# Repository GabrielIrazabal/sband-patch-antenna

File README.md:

# S-band patch antenna (SSI 1U CubeSat), rev 1

Right-hand circularly polarized patch antenna for the satellite's S-band TT&C link (uplink and downlink, around 2.4 GHz). This repo holds the rev-1 KiCad boards, order-ready Gerbers, the simulations behind them and the design notes.

Research doc: PJ-10004, S-band patch antenna research (internal to SSI) · Author: Gabriel Irazabal

> **Using an AI assistant?** Point it at this repo. It should read [`CLAUDE.md`](CLAUDE.md) first.
>
> **Running the Ansys HFSS check on the Windows laptop?** Everything is in [`HFSS_TASK.md`](HFSS_TASK.md).

## Status

| Step | State |
| --- | --- |
| Requirements and design decisions | Done |
| Simulation (openEMS) | Done for five boards: two designs × two materials, plus a cut-corner PTFE board tuned for the satellite face |
| KiCad boards, size variants, Gerbers | Done for all four antenna options below, zips in [`fab/`](fab). The 3 mm boards still have open questions for JLC |
| **Decision needed: board material** | RO4350B does not reach the 6.5 dBic gain requirement; JLC's PTFE does once mounted on the satellite. See [Gain](#gain-the-one-requirement-not-met-on-ro4350b) |
| Cross-check in HFSS | Done. HFSS agrees within 0.4 % in frequency and 0.3 dB in gain. See [`sim/HFSS_RESULTS.md`](sim/HFSS_RESULTS.md) |
| Rerun check, 24 November | All four re-simulated in openEMS: three pass in both solvers, the 1.5 mm dual feed is borderline. See [`sim/RERUN_CHECK.md`](sim/RERUN_CHECK.md). HFSS rerun on the laptop: [`HFSS_RERUN.md`](HFSS_RERUN.md) |
| JLC order, VNA test | Not done |

## The four antenna options and their files

All four are on JLC's PTFE (ZYF255DA), 60 × 60 mm, tuned in HFSS for 2.425 GHz on a 100 mm metal face. Numbers are HFSS, across the 20 MHz channel; nothing has been built. Plots: [`docs/results_60mm/`](docs/results_60mm/README.md).

| Antenna | Patch / feed / cut (mm) | RHCP gain | Worst axial ratio | KiCad | Gerbers |
| --- | --- | --- | --- | --- | --- |
| Cut corner, 1.5 mm | 37.52 / 7.00 / 3.50 | 7.08–7.24 dBic | 4.14 dB | [`kicad/Cutcorner_antenna`](kicad/Cutcorner_antenna) (drawn by hand) | `fab/Cutcorner_antenna.zip` |
| Dual feed, 1.5 mm | 37.28 / 5.80 / none | 6.75–6.96 dBic | 0.79 dB | [`kicad/A_dualfeed_PTFE_face100`](kicad/A_dualfeed_PTFE_face100) | `fab/A_dualfeed_PTFE_face100.zip`, plus `_L36p98` and `_L37p58` |
| Cut corner, 3 mm | 37.10 / 8.00 and 2.18 sideways / 5.55 | 7.61–7.67 dBic | 2.17 dB | [`kicad/prototype_thick`](kicad/prototype_thick): `B_cutcorner_RHCP_PTFE_3mm_TOP` and `_BOTTOM` | `fab/B_cutcorner_RHCP_PTFE_3mm_TOP.zip` and `_BOTTOM.zip` |
| Dual feed, 3 mm | 36.39 / 6.70 / none | 7.26–7.32 dBic | 0.94 dB | [`kicad/prototype_thick`](kicad/prototype_thick): `A_dualfeed_PTFE_3mm_TOP` and `_BOTTOM` | `fab/A_dualfeed_PTFE_3mm_TOP.zip` and `_BOTTOM.zip` |

- Dual-feed figures assume a typical 90° coupler (0.5 dB and 3° off, 0.4 dB loss). The coupler is an external part.
- **The 1.5 mm cut corner here is the hand-drawn board.** It has the same dimensions as the generated `B_cutcorner_RHCP_PTFE_face100`, with the whole top side free of solder mask. The generated board and its ±0.3 mm variants are still in `kicad/` and `fab/`.
- **The 3 mm antennas are each two boards** glued face to face: a TOP board with only the patch and a BOTTOM board with only the ground and connector. Read the open points in [`kicad/prototype_thick/README.md`](kicad/prototype_thick/README.md) before ordering them.
- **These sizes are for PTFE only.** On RO4350B the same patch would resonate near 2.04 GHz. The RO4350B boards are the ones in the table under [The boards](#the-boards).
- Every board except the generated rev-1 ones has its whole top side free of solder mask, because HFSS showed mask around the patch shifts the tuning by 6 to 8 MHz.

## Requirements and how the designs compare

Simulated on the bare 60 × 60 mm board at 2.425 GHz. Board A assumes an ideal 90° hybrid.

| Requirement | Target | A, RO4350B | B, RO4350B | A, PTFE | B, PTFE |
| --- | --- | --- | --- | --- | --- |
| Frequency | 2.4 GHz band (design centre 2.425 GHz) | ✓ | ✓ | ✓ | ✓ |
| Match across 20 MHz | return loss ≥ 10 dB | ✓ 13.5 dB | ✓ 12.2 dB | ✓ 14.3 dB | ✓ 11.6 dB |
| Gain | ≥ 6.5 dBic, ideally 7+ | ✗ 5.6–5.8 | ✗ 5.5–5.7 | ✗ 6.3–6.4 | ✗ 6.1–6.3 |
| Gain on a 100 mm metal face | same | ✗ 5.9–6.0 | ✗ 6.0–6.1 | ✓ 6.8–6.9 | ✓ 6.7–6.9 |
| Half-power beamwidth | ≥ 60° | ✓ 88° | ✓ 88° | ✓ 84° | ✓ 84° |
| Polarization | RHCP | ✓ | ✓ | ✓ | ✓ |
| Axial ratio across 20 MHz | ≤ 3 dB | set by the hybrid | ✗ 3.5 dB at the edges | set by the hybrid | ✗ 3.4 dB at the edges |
| Impedance | 50 Ω | ✓ | ✓ | ✓ | ✓ |
| Power handling | ≥ 3 W | SMA: yes. Not otherwise analysed | | | |
| Environment | −40 to +85 °C | Not simulated directly; see drift below | | | |
| Connector | SMA | ✓ surface-mount vertical SMA | | | |

Notes on reading this table:
- **Board A's gain is before the hybrid's own loss**, typically 0.3–0.5 dB. Board B has no hybrid.
- **Board A's axial ratio** depends on the hybrid's amplitude and phase balance, not on the patch. With both ports simulated separately the patch itself gives 0.2–0.3 dB.
- **A 3.4–3.5 dB axial ratio at the band edge** costs about 0.15 dB against a perfectly circular ground antenna.
- **The 60° beamwidth target** is met with margin: at 30° off boresight the gain is down about 1.5 dB (2.0–2.2 dB on the 100 mm face).

## Gain: the one requirement not met on RO4350B

The patch's directivity is fixed mostly by its size and ground plane. What's left after losses in the board and copper is the gain.

Best achievable gain (directivity × radiation efficiency, perfect match, no hybrid loss):

| Material, thickness | Directivity | Efficiency | Bare 60 mm board | On a 100 mm metal face |
| --- | --- | --- | --- | --- |
| RO4350B, 1.52 mm | 6.7 dBi | 82–84 % | 5.9 dBic | 6.3 dBic |
| RO4350B, 3.05 mm (two boards stacked) | 6.7 dBi | 91 % | 6.3 dBic | 6.8 dBic |
| PTFE ZYF255DA, 1.52 mm | 7.1 dBi | 89 % | 6.6 dBic | 7.2 dBic |
| PTFE ZYF255DA, 3.05 mm (stacked) | 7.1 dBi | 94 % | 6.8 dBic | 7.5 dBic |

- **RO4350B at 1.52 mm cannot reach 6.5 dBic** in any simulated configuration.
- **PTFE at 1.52 mm reaches it once mounted on the satellite**: the larger patch (about 37 mm) has more directivity, and the material loses less.
- **A cut-corner PTFE board tuned for the 100 mm face reaches 6.8–7.05 dBic** across the band (`B_cutcorner_RHCP_PTFE_face100`). That is the only simulated 1.52 mm board that touches "ideally 7+"; getting comfortably past 7 needs PTFE and more thickness.
- The 100 mm face is modeled as a flat metal plate behind the board. A real 1U body with solar panels will differ somewhat.
- Mission Control's link budget assumed a 5 dBi linear patch with a 3 dB polarization loss. Every board here beats that assumption.

Trade-offs of moving to PTFE (ZYF255DA):

| | RO4350B | ZYF255DA (PTFE) |
| --- | --- | --- |
| Dk / loss tangent | 3.66 (design) / 0.0031 | 2.55 / 0.0018 (JLC listing) |
| Patch side at 2.425 GHz | 31.4 mm | 37.4 mm (fits the 60 mm board) |
| Gain | about 0.7 dB lower | about 0.7 dB higher |
| JLC price | about $185 for 5 | lower when quoted in October |
| Space heritage, outgassing data | widely flown; TML 0.12 %, CVCM 0.02 % | **no outgassing data found for this laminate** |
| Dk used for design | Rogers publishes a design value | JLC's listed value, not independently verified |

## The boards

| | Top | Bottom |
| --- | --- | --- |
| **A: dual feed** (RO4350B) |  |  |
| **B: cut corner** (RO4350B) |  |  |
| **A-PTFE** |  |  |
| **B-PTFE** |  |  |

Simulated dimensions (mm):

| Board | Patch side | Feed offset from centre | Corner cut leg | Size variants built |
| --- | --- | --- | --- | --- |
| `A_dualfeed` | 31.40 | 5.80 | none | 31.10, 31.70 |
| `B_cutcorner_RHCP` | 31.54 | 5.90 | 3.13 | 31.24, 31.84 |
| `A_dualfeed_PTFE` | 37.38 | 6.90 | none | 37.08, 37.68 |
| `B_cutcorner_RHCP_PTFE` | 37.56 | 7.00 | 3.80 | 37.26, 37.86 |
| `B_cutcorner_RHCP_PTFE_face100` | 37.52 | 7.00 | 3.50 | 37.22, 37.82 |

`B_cutcorner_RHCP_PTFE_face100` looks the same as B-PTFE but is tuned for mounting flat on a 100 mm metal face. On that face it simulates at 0.2 dB best axial ratio at 2.425 GHz, 3.9 dB at the band edges, and 6.8–7.05 dBic. Use it only if the antenna really mounts that way.

Common to all:
- 60 × 60 mm, 2 layers, 1.52 mm core, ENIG.
- **Top:** only the patch, with no solder mask over it.
- **Bottom:** solid ground, M3 mounting holes 4 mm from each corner (placeholder positions).
- **Feed:** surface-mount vertical SMA (Würth WR-SMA 60312102114405) on the bottom, soldered flat to the ground so no legs pass through the patch. A 0.5 mm plated via under its centre pad is the probe up to the patch.
- **Board A:** J1 on the +x axis, J2 on the +y axis (up in the top view). **RHCP when J2 lags J1 by 90°**; this is printed on the back. It has no hybrid on the board: test it with an external connectorized 90° hybrid and two equal-length cables.
- **Board B:** top-left and bottom-right corners cut (top view). **Confirmed RHCP** two ways: from the simulated far field, and from the rotation of the raw field over time above the patch.
- The size variants cover frequency error: 0.3 mm of patch side is about 21 MHz on RO4350B and 19 MHz on PTFE.

## Simulation results

Solver: openEMS (FDTD). Details and the full run list are in [`sim/README.md`](sim/README.md); raw outputs are in [`sim/results_openems/`](sim/results_openems).

| Board | Plot |
| --- | --- |
| A, RO4350B |  |
| B, RO4350B |  |
| A, PTFE |  |
| B, PTFE |  |

Detail (bare 60 mm board unless stated):

| | A, RO4350B | B, RO4350B | A, PTFE | B, PTFE |
| --- | --- | --- | --- | --- |
| Worst S11 in the 20 MHz band | −13.5 dB | −12.2 dB | −14.3 dB | −11.6 dB |
| −10 dB match bandwidth | 35.5 MHz | 69 MHz | 37.5 MHz | 71 MHz |
| Isolation between ports | −39 dB | n/a | −39 dB | n/a |
| Best axial ratio | hybrid-set | 0.2 dB | hybrid-set | 0.3 dB |
| Axial ratio ≤ 3 dB bandwidth | hybrid-set | about 15–18 MHz | hybrid-set | about 15–18 MHz |
| RHCP gain in band | 5.6–5.8 dBic | 5.5–5.7 dBic | 6.3–6.4 dBic | 6.1–6.3 dBic |
| RHCP gain on the 100 mm face | 5.9–6.0 dBic | 6.0–6.1 dBic | 6.8–6.9 dBic | 6.7–6.9 dBic |
| Half-power beamwidth (on the 100 mm face) | 88° (74–76°) | 88° (74–76°) | 84° (72–74°) | 84° (72–74°) |

### Sensitivity to board material (Dk off by ±1 %)

| | A, RO4350B | B, RO4350B | A, PTFE | B, PTFE |
| --- | --- | --- | --- | --- |
| Frequency shift | ±12.5 MHz | ±12.5 MHz | ±11.5 MHz | ±11.5 MHz |
| Worst S11 in band | −8.5 dB | −10 dB | −9.2 dB | −10.2 dB |
| Worst axial ratio in band | unaffected | 7.5 dB | unaffected | 6.8 dB |
| Lowest RHCP gain in band | 5.2 dBic | 4.8 dBic | 5.95 dBic | 5.6 dBic |

Board A tolerates material and temperature drift better: its polarization is set by the hybrid, so a frequency shift only costs some match. Board B's polarization degrades directly.

### Effect of the ground it's mounted on

A larger ground raises gain by about 0.5 dB and narrows the resonance (RO4350B match bandwidth 36 → 26 MHz). On the 100 mm face, board B's best axial ratio degrades from 0.2–0.3 dB to 1.3–1.5 dB because its corner cut was tuned for the bare board. **Board B needs re-tuning for the real mounting; board A does not.**

Re-tuning works as predicted: shrinking the PTFE board's cut from 3.80 to 3.50 mm (and the patch from 37.56 to 37.52 mm) brought the axial ratio on the 100 mm face back to 0.2 dB at 2.425 GHz.

### What the simulation does and doesn't establish

- **Frequency accuracy is about ±1 %.** Two published measured patches on εr 2.5, 1.524 mm board simulate 0.4–0.9 % low: 41.4 × 41.0 mm (measured 2.228 GHz, simulated 2.208–2.217) and 41.4 × 68.58 mm (measured 2.200 GHz, simulated 2.185–2.192). The measured values were recalled from the literature, not re-read, so treat this as supporting evidence.
- **Real boards may therefore land 10–20 MHz high.** If so, the +0.3 mm variant of each board will be the one closest to 2.425 GHz. That's why the variants are worth ordering.
- **The hand formulas read about 2.7 % high** for these boards. They put the RO4350B patch at 32.12 mm; the simulation puts it at 31.40 mm. A finer mesh gives the same answer within 2.5 MHz.
- **Not modeled:** the SMA body, the via's true diameter (the probe is a thin wire, which overstates its inductance by roughly 6 Ω), solder mask, ENIG, a real hybrid, and the real satellite body.
- **PTFE inputs are JLC's listed values** (Dk 2.55, Df 0.0018), not measured ones.

## Design decisions

| Decision | Choice | Why |
| --- | --- | --- |
| Board size | 60 × 60 mm | Leaves 11–14 mm of ground around the patch |
| Thickness | 1.52 mm | Thickest single JLC option; more bandwidth and efficiency than thinner cores |
| Fab | JLC, 2-layer high-frequency | JLC offers RO4350B and its PTFE line as 2-layer only |
| Polarization | RHCP, IEEE convention, wave leaving the satellite | Confirmed by the team. The dish reflection flips the hand of the ground feed, so "RHCP" always means the transmitted wave |
| Circular polarization method | Build both: dual feed + hybrid (A) and cut corner (B) | A covers the full 20 MHz and tolerates drift; B is simpler but narrower |
| Hybrid location for rev 1 | Off the board (external) | A 2-layer board has no clean layer for the hybrid and its feed lines. Where it lives is a rev-2 decision |
| Connector | Surface-mount vertical SMA | Threaded and the CubeSat norm; surface-mount so nothing passes through the patch. It sticks out about 10 mm behind the board |

Polarization loss against a perfectly circular ground antenna, by axial ratio:

| Axial ratio | 1 dB | 3 dB | 6 dB | 10 dB | linear |
| --- | --- | --- | --- | --- | --- |
| Loss | 0.01 dB | 0.13 dB | 0.45 dB | 1.04 dB | 3 dB |

## How to

### Regenerate the boards

Install KiCad 10, then run its bundled Python:

```bash
"C:\Program Files\KiCad\10.0\bin\python.exe" kicad/generate_boards.py
```

On macOS use `/Applications/KiCad/KiCad.app/Contents/Frameworks/Python.framework/Versions/Current/bin/python3`.

Every dimension lives in `BOARDS` / `COMMON` at the top of `kicad/generate_boards.py`. The script rebuilds each board, refills the ground, runs DRC and updates `docs/renders/`. Options:
- `--variants -0.3 0.3` builds patch-size variants.
- `--gerbers` writes JLC zips to `fab/`.
- `--only A_dualfeed` builds one board.

Hand edits to the `.kicad_pcb` files are overwritten on the next run.

### Simulate

See [`sim/README.md`](sim/README.md).

### Order from JLC

Upload each zip from [`fab/`](fab), then set:
- **Material:** Rogers RO4350B, or PTFE ZYF255DA for the `_PTFE` boards
- **Thickness:** 1.52 mm
- **Layers:** 2
- **Surface finish:** ENIG
- **Copper:** 1 oz
- **Via-in-pad:** ask for the probe via under the SMA centre pad to be filled and capped. Otherwise hand-solder carefully so solder doesn't wick down the via.

Each rev-1 design has three zips: nominal, −0.3 mm and +0.3 mm. Order about 5 of each version you want to test.

For the 3 mm antennas, order the TOP and BOTTOM zips as two separate boards with the same settings, and read [`kicad/prototype_thick/README.md`](kicad/prototype_thick/README.md) first.

### Test (on a VNA)

| Test | How |
| --- | --- |
| Match | S11 at each port; S21 between board A's two ports |
| Circular polarization | Rotate a linear antenna in front of the patch and record received power. Less variation means better circular polarization |
| Hand | A known RHCP antenna should receive far more than an LHCP one |
| Gain (rough) | Compare against a known antenna |

Stand the board on M3 standoffs: the SMA sticks out the back.

## Open items

| Item | Owner |
| --- | --- |
| **Board material:** RO4350B (heritage, 5.9–6.3 dBic) or PTFE ZYF255DA (6.6–7.2 dBic, no outgassing data found) | Gabriel / TT&C lead |
| Is 6.5 dBic a hard requirement? The link budget assumed 5 dBi | Mission Control |
| Exact carrier frequency and signal bandwidth (design assumes 2.425 GHz, 20 MHz) | TT&C lead |
| How the antenna mounts: which face, what metal is behind it, depth available for the SMA and cable | Structures / GNC |
| Mounting-hole pattern (M3 at 4 mm from the corners is a placeholder) | Structures |
| Hybrid location and part for rev 2 | TT&C lead |
| A connectorized 2.4 GHz 90° hybrid and two equal-length SMA cables for bench testing | TT&C lead / lab |
| Outgassing data for ZYF255DA, if PTFE is chosen | Gabriel |
| Solder mask on the top side: HFSS shows mask around the patch shifts the tuning by about −6 to −8 MHz ([`sim/HFSS_RESULTS.md`](sim/HFSS_RESULTS.md)). Ask JLC whether the top can be left free of mask | Gabriel |

## Reference design

Samsuzzaman et al., ["Right hand circularly polarized 2.40 GHz truncated corner patch antenna for small satellite application"](https://joam.inoe.ro/articles/right-hand-circularly-polarized-240-ghz-truncated-corner-patch-antenna-for-small-satellite-application/fulltext) (JOAM).

- Same as ours: 2.40 GHz, a single square patch over a ground plane, cut corners, a coax probe from behind, about 6.7 dBi, designed in HFSS, built and measured on a VNA.
- Different from ours: Rogers RT5880 (a PTFE laminate, εr 2.2), and a narrow channel with an axial-ratio bandwidth of about 2 MHz. Their gain on a low-loss PTFE board is consistent with the PTFE results here.

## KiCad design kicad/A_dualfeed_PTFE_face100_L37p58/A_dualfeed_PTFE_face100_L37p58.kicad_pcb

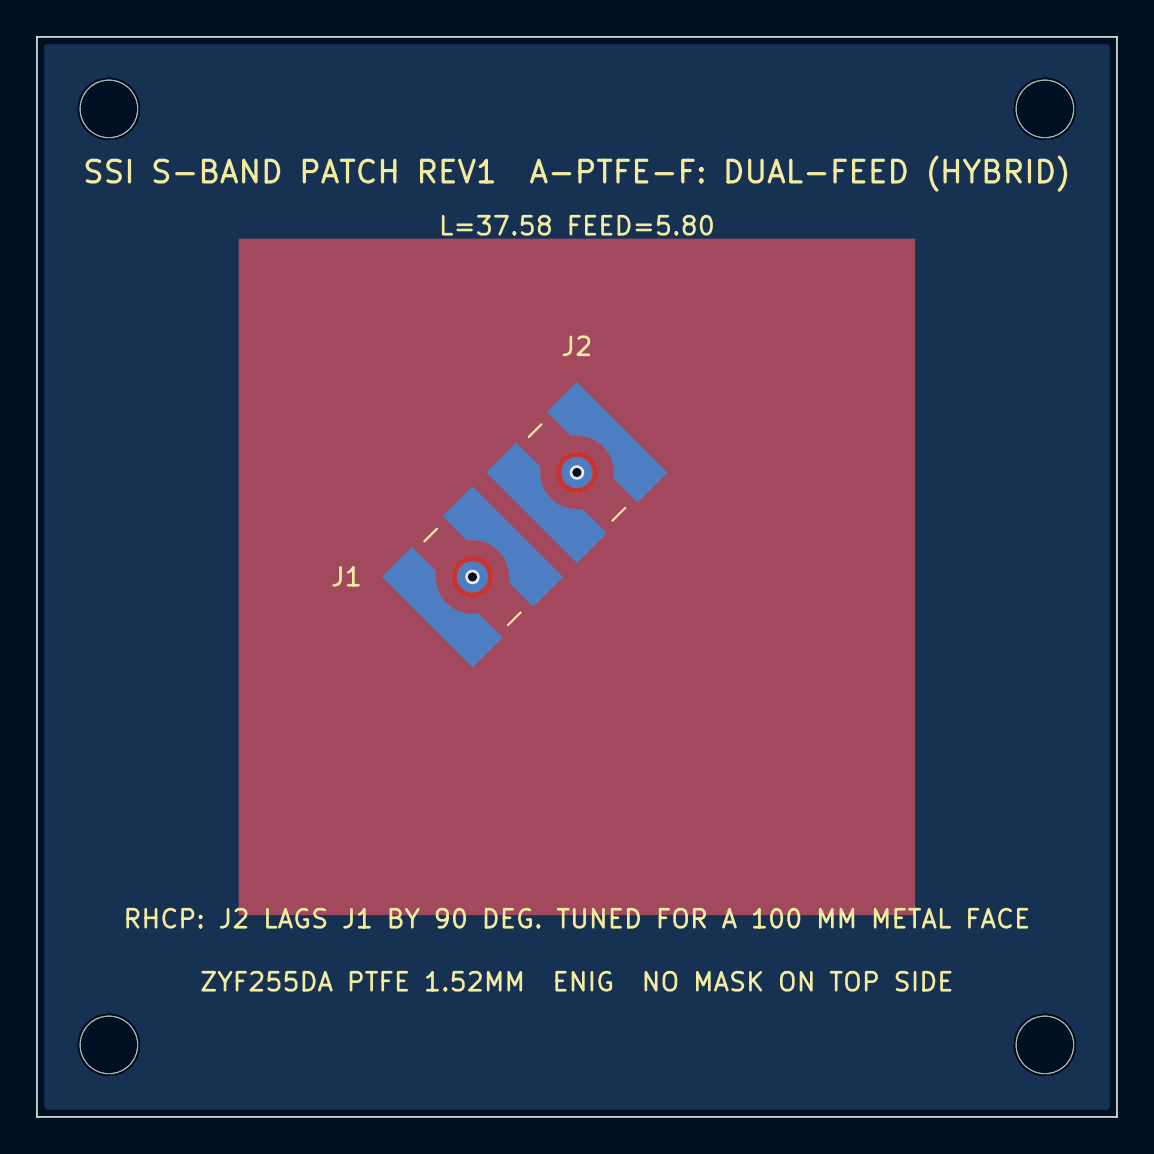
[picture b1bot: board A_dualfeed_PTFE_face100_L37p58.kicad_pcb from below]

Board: 2 copper layers, 60.0 x 60.0 mm, 6 parts (2 on the bottom side), 2 nets, no tracks yet.

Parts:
H1, H2, H3, H4: MountingHole_3.2mm_M3
J1, J2: Wurth WR-SMA 60312102114405; SMA_Wurth_60312102114405_Vertical

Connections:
GND: J1.2, J2.2
PATCH: J1.1, J2.1
